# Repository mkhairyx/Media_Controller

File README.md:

# Gesture Based Media controller

## What is it
It's a device that controls your TV using IR signals to mimic your TV's remote control. It detects a gesture and then sends the signal that was coded for that gesture.

## The reason I made it
I made it so I can control different media without having to touch anything with my dirty hands while eating.

## Main modules used
- MCU: An ESP32
- Gesture Sensor: PAJ7620
- Display: OLED 0.96" SSD1306 Display

## Pins and their usages
- GPIO4: IR LED
- GPIO15: IR receiver (TL1838)
- GPIO21: SDA (for both the Gesture Sensor and the display)
- GPIO22: SCL (for both the Gesture Sensor and the display)
- GPIO18: delete button (Internally pulled high)

## How to recreate
You can either make the PCB with is [here](./source/pcbway_production/) or connect everything on a breadboard (while using [this](./README.md#pins-and-their-usages) as a reference) then you can flash the software provided [here](./Source/Arduino/Media_Controller_IRTXnRX) to your ESP32.

## Gestures and their functions
- Move Up / Move Down:<br>
Up Button / Down Button
- Move Left / Move Right:<br>
Left Button / Right Button
- Move Forward:<br>
OK button (for TV)
- Circle Clockwise (CW) / Circle Counter-Clockwise (CCW):<br>
Volume Up Button / Volume Down Button
- Wave (shake):<br>
switch between different TV/PC (Inoperative for now, PC functions will be available in V2)

## Demo Video
A demo vid can be watched here:<br>
https://youtu.be/PJmMg9s-Np0
https://cdn.hackclub.com/01a003da-1a12-7c9f-beef-b3fb1ff95faa/Media%20Controller%20Demo-2.mp4

## Notes
- Please note that AI was used to help with **some** parts of the code and not all of it.
- This is the first version of this project and it doesn't have all of the functions. V2 will have battery percentage measurement, better UI, and will be compatible with both TV and PC with the ability to switch between them.

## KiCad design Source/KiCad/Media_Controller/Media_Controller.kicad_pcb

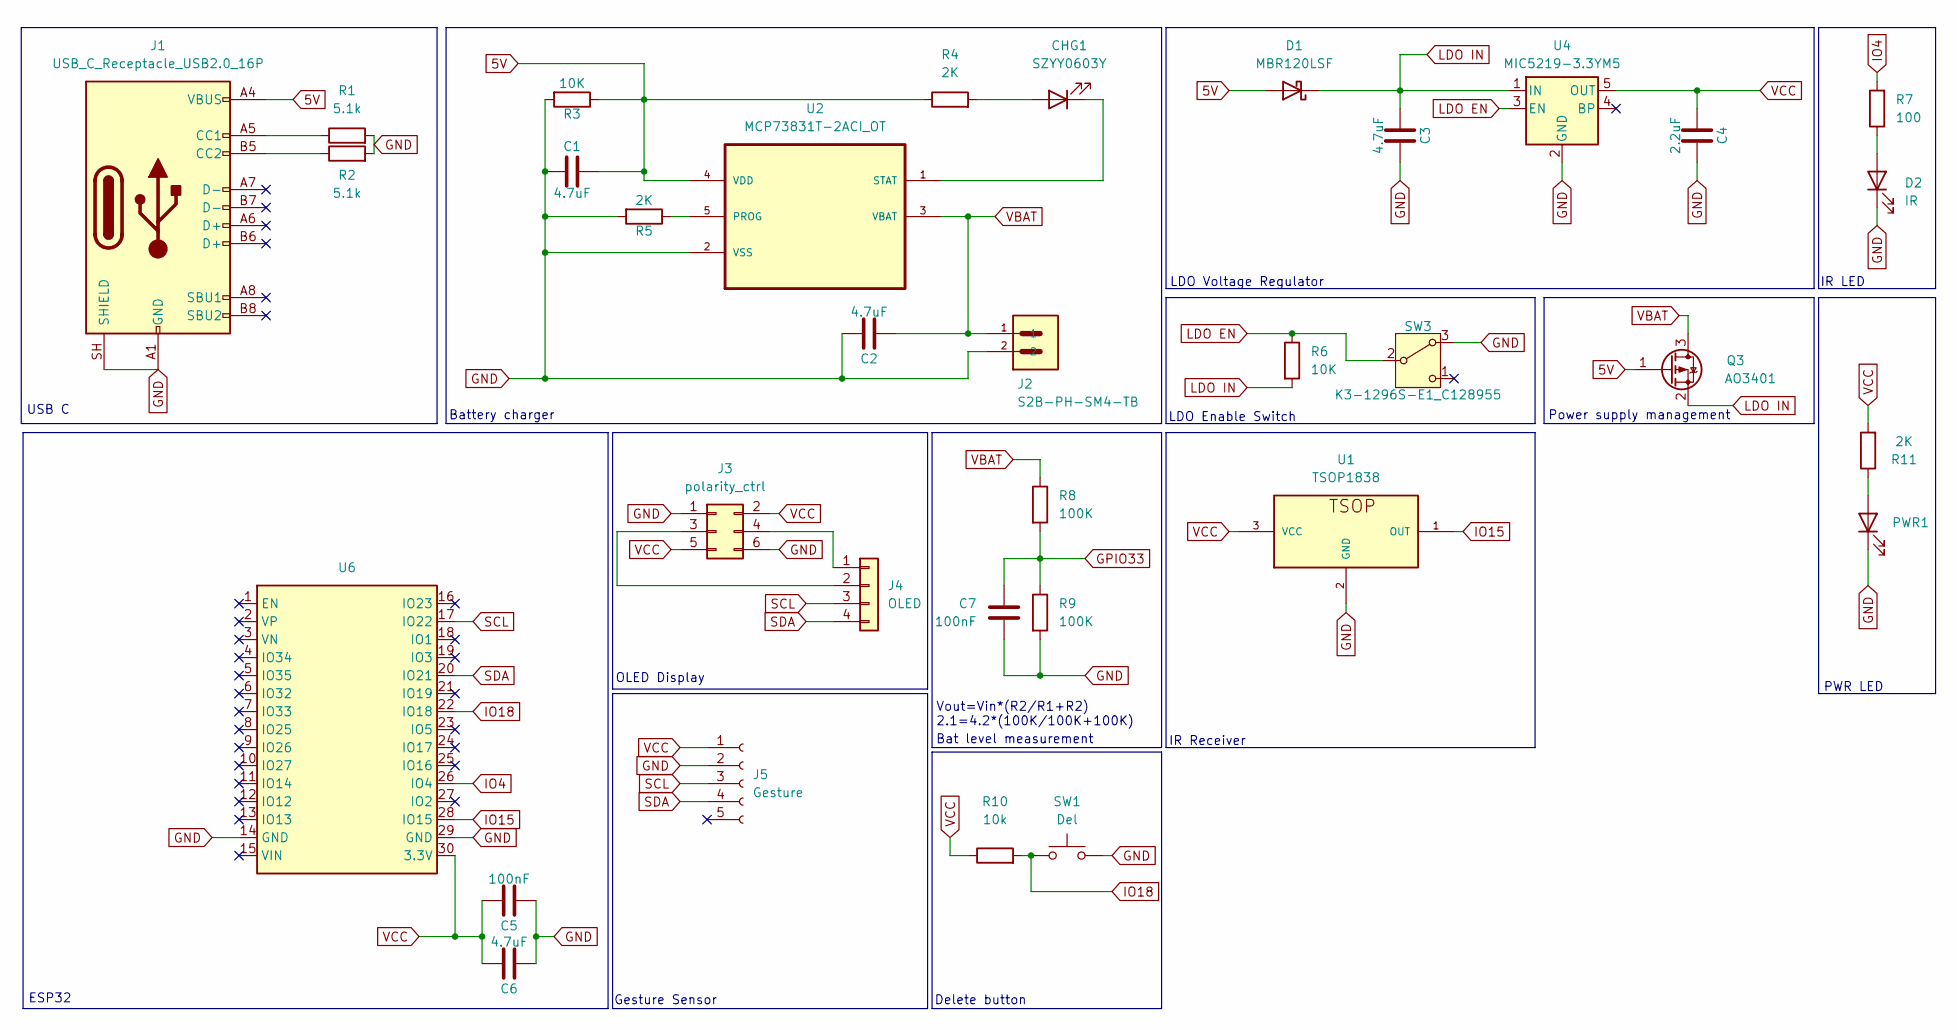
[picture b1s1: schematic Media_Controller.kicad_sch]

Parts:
C1, C2, C3, C6: 4.7uF; C_1206_3216Metric_Pad1.33x1.80mm_HandSolder
C4: 2.2uF; C_0805_2012Metric_Pad1.18x1.45mm_HandSolder
C5, C7: 100nF; C_1206_3216Metric_Pad1.33x1.80mm_HandSolder
CHG1: SZYY0603Y; LED_0805_2012Metric_Pad1.15x1.40mm_HandSolder
D1: MBR120LSF; D_SMA_Handsoldering
D2: IR; LED_D5.0mm
J1: USB_C_Receptacle_USB2.0_16P; USB_C_Receptacle_GCT_USB4105-xx-A_16P_TopMnt_Horizontal
J2: S2B-PH-SM4-TB; JST_EH_B2B-EH-A_1x02_P2.50mm_Vertical
J3: polarity_ctrl; PinHeader_2x03_P2.54mm_Vertical
J4: OLED; PinSocket_1x04_P2.54mm_Vertical
J5: Gesture; PinSocket_1x05_P2.54mm_Vertical
PWR1: SZYY0603Y; LED_0805_2012Metric_Pad1.15x1.40mm_HandSolder
Q3: AO3401; SOT-23
R1, R2: 5.1k; R_Axial_DIN0207_L6.3mm_D2.5mm_P7.62mm_Horizontal
R3, R6: 10K; R_0805_2012Metric_Pad1.20x1.40mm_HandSolder
R4, R5, R11: 2K; R_0805_2012Metric_Pad1.20x1.40mm_HandSolder
R7: 100; R_0805_2012Metric_Pad1.20x1.40mm_HandSolder
R8, R9: 100K; R_0805_2012Metric_Pad1.20x1.40mm_HandSolder
R10: 10k; R_0805_2012Metric_Pad1.20x1.40mm_HandSolder
SW1: Del; SW_PUSH_6mm_H13mm
SW3: K3-1296S-E1_C128955; SW_Slide_SPDT_Angled_CK_OS102011MA1Q
U1: TSOP1838
U2: MCP73831T-2ACI_OT; SOT-23-5_HandSoldering; MPN MCP73831T-2ACI/OT
U4: MIC5219-3.3YM5; SOT-23-5_HandSoldering
U6: ESP32 DevKit

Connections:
5V: C1.2, D1.2 (A), J1.A4 (VBUS), J1.A9 (VBUS), J1.B4 (VBUS), J1.B9 (VBUS), Q3.1 (G), R3.1, R4.1, U2.4 (VDD)
GND: C1.1, C2.2, C3.2, C4.2, C5.1, C6.1, C7.2, D2.1 (K), J1.A1 (GND), J1.A12 (GND), J1.B1 (GND), J1.B12 (GND), J1.SH (SHIELD), J2.2, J3.1, J3.6, J5.2, PWR1.1 (K), R1.2, R2.2, R3.2, R5.2, R9.2, SW1.2, SW3.3 (A), U1.2 (GND), U2.2 (VSS), U4.2 (GND), U6.14 (GND), U6.29 (GND)
GPIO33: C7.1, R8.2, R9.1
IO4: R7.2, U6.26 (IO4)
IO15: U1.1 (OUT), U6.28 (IO15)
IO18: R10.2, SW1.1, U6.22 (IO18)
LDO EN: R6.1, SW3.2 (B), U4.3 (EN)
LDO IN: C3.1, D1.1 (K), Q3.2 (S), R6.2, U4.1 (IN)
unnamed: CHG1.2 (A), R4.2
unnamed: CHG1.1 (K), U2.1 (STAT)
unnamed: D2.2 (A), R7.1
unnamed: J1.A5 (CC1), R1.1
unnamed: J1.B5 (CC2), R2.1
unnamed: J3.3, J4.2
unnamed: J3.4, J4.1
unnamed: PWR1.2 (A), R11.1
unnamed: R5.1, U2.5 (PROG)
SCL: J4.3, J5.3, U6.17 (IO22)
SDA: J4.4, J5.4, U6.20 (IO21)
VBAT: C2.1, J2.1, Q3.3 (D), R8.1, U2.3 (VBAT)
VCC: C4.1, C5.2, C6.2, J3.2, J3.5, J5.1, R10.1, R11.2, U1.3 (VCC), U4.5 (OUT), U6.30 (3.3V)

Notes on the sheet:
PWR LED
OLED Display
Delete button
LDO Enable Switch
Gesture Sensor
Power supply management
ESP32
IR Receiver
IR LED
Battery charger
Bat level measurement
USB C
Vout=Vin*(R2/R1+R2) 2.1=4.2*(100K/100K+100K)
LDO Voltage Regulator

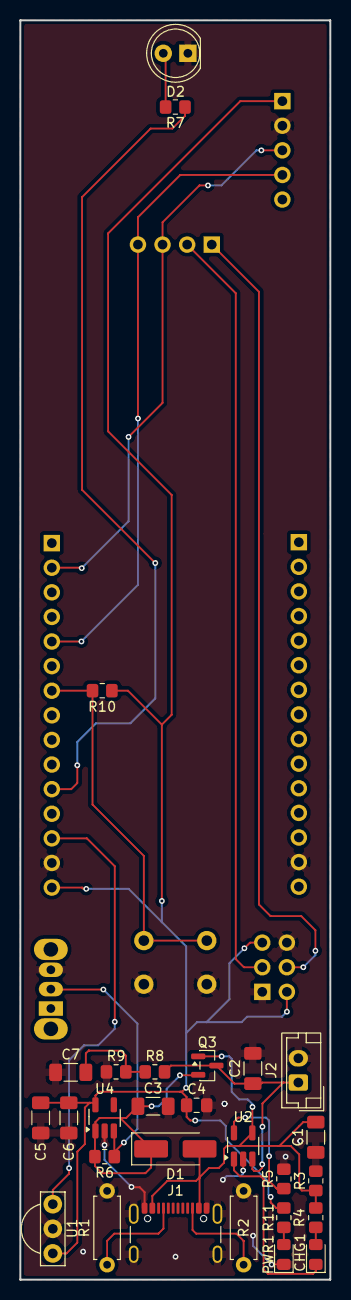
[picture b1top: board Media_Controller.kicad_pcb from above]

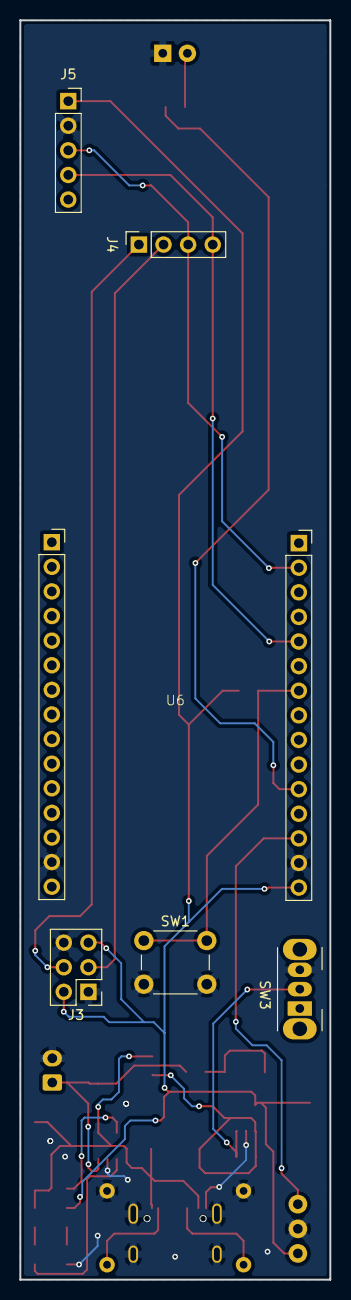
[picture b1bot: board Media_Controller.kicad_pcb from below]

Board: 2 copper layers, 32.0 x 130.0 mm, 34 parts (6 on the bottom side), 21 nets.

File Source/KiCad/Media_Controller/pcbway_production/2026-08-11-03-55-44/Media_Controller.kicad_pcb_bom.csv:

Designator,Quantity,Value,Footprint,Package,MPN,DNP,Mount_Type,Description,KiLib_Generator,Sim.Pins,MF,Price,Check_prices,SnapEDA_Link,MP,Purchase-URL,Availability,MANUFACTURER,OC_FARNELL,SUPPLIER,OC_NEWARK
"C1, C2, C3, C6",4,4.7uF,C_1206_3216Metric_Pad1.33x1.80mm_HandSolder,,,,smt,Unpolarized capacitor,SMD_2terminal_chip_molded,,,,,,,,,,,,
C4,1,2.2uF,C_0805_2012Metric_Pad1.18x1.45mm_HandSolder,,,,smt,Unpolarized capacitor,SMD_2terminal_chip_molded,,,,,,,,,,,,
"C5, C7",2,100nF,C_1206_3216Metric_Pad1.33x1.80mm_HandSolder,,,,smt,Unpolarized capacitor,SMD_2terminal_chip_molded,,,,,,,,,,,,
"CHG1, PWR1",2,SZYY0603Y,LED_0805_2012Metric_Pad1.15x1.40mm_HandSolder,,,,smt,Light emitting diode,SMD_2terminal_chip_molded,1=K 2=A,,,,,,,,,,,
D1,1,MBR120LSF,D_SMA_Handsoldering,,,,smt,Schottky diode,,,,,,,,,,,,,
D2,1,IR,LED_D5.0mm,,,,tht,Light emitting diode,LED/THT,1=K 2=A,,,,,,,,,,,
J1,1,USB_C_Receptacle_USB2.0_16P,USB_C_Receptacle_GCT_USB4105-xx-A_16P_TopMnt_Horizontal,,,,smt,USB 2.0-only 16P Type-C Receptacle connector,,,,,,,,,,,,,
J2,1,S2B-PH-SM4-TB,JST_EH_B2B-EH-A_1x02_P2.50mm_Vertical,None,,,tht,"Connector Header Surface Mount, Right Angle 2 position 0.079 (2.00mm)",connector/JST,,JST Sales,None,https://www.snapeda.com/parts/S2B-PH-SM4-TB/JST/view-part/?ref=eda,https://www.snapeda.com/parts/S2B-PH-SM4-TB/JST/view-part/?ref=snap,S2B-PH-SM4-TB,https://www.snapeda.com/api/url_track_click_mouser/?unipart_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 Sales&part_name=S2B-PH-SM4-TB&search_term=s2b-ph-sm4-tb,In Stock,JST,,,
J3,1,polarity_ctrl,PinHeader_2x03_P2.54mm_Vertical,,,,tht,"Generic connector, double row, 02x03, odd/even pin numbering scheme (row 1 odd numbers, row 2 even numbers), script generated (kicad-library-utils/schlib/autogen/connector/)",connector/pin_header_socket,,,,,,,,,,,,
J4,1,OLED,PinSocket_1x04_P2.54mm_Vertical,,,,tht,"Generic connector, single row, 01x04, script generated (kicad-library-utils/schlib/autogen/connector/)",connector/pin_header_socket,,,,,,,,,,,,
J5,1,Gesture,PinSocket_1x05_P2.54mm_Vertical,,,,tht,"Generic connector, single row, 01x05, script generated",connector/pin_header_socket,,,,,,,,,,,,
Q3,1,AO3401,SOT-23,,,,smt,"-0.18A Id, -60V Vds, P-Channel MOSFET, SOT-23",package/gullwing,,,,,,,,,,,,
"R1, R2",2,5.1k,R_Axial_DIN0207_L6.3mm_D2.5mm_P7.62mm_Horizontal,,,,tht,Resistor,resistor/THT,,,,,,,,,,,,
R10,1,10k,R_0805_2012Metric_Pad1.20x1.40mm_HandSolder,,,,smt,Resistor,SMD_2terminal_chip_molded,,,,,,,,,,,,
"R11, R4, R5",3,2K,R_0805_2012Metric_Pad1.20x1.40mm_HandSolder,,,,smt,Resistor,SMD_2terminal_chip_molded,,,,,,,,,,,,
"R3, R6",2,10K,R_0805_2012Metric_Pad1.20x1.40mm_HandSolder,,,,smt,Resistor,SMD_2terminal_chip_molded,,,,,,,,,,,,
R7,1,100,R_0805_2012Metric_Pad1.20x1.40mm_HandSolder,,,,smt,Resistor,SMD_2terminal_chip_molded,,,,,,,,,,,,
"R8, R9",2,100K,R_0805_2012Metric_Pad1.20x1.40mm_HandSolder,,,,smt,Resistor,SMD_2terminal_chip_molded,,,,,,,,,,,,
SW1,1,Del,SW_PUSH_6mm_H13mm,,,,tht,"Push button switch, generic, two pins",,,,,,,,,,,,,
SW3,1,K3-1296S-E1_C128955,SW_Slide_SPDT_Angled_CK_OS102011MA1Q,,,,tht,"Switch slide, single pole double throw",,,,,,,,,,,,,
U1,1,TSOP1838,TSOP1838,None,,,tht,IR Remote Receiver 38KHz 35m 3-Pin,,,Vishay,None,https://www.snapeda.com/parts/TSOP1838/Vishay/view-part/?ref=eda,https://www.snapeda.com/parts/TSOP1838/Vishay/view-part/?ref=snap,TSOP1838,https://www.snapeda.com/api/url_track_click_mouser/?unipart_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,In Stock,,,,
U2,1,MCP73831T-2ACI_OT,SOT-23-5_HandSoldering,SOT-5,MCP73831T-2ACI/OT,,smt,"TINY INTEGRATED LI-ION/LI-POLY CHARGE MGNT CONTROLLER, 4.2V VREG | Microchip Technology Inc. MCP73831T-2ACI/OT",,,Microchip,None,https://www.snapeda.com/parts/MCP73831T-2ACI/OT/Microchip+Te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,https://www.snapeda.com/parts/MCP73831T-2ACI/OT/Microchip+Te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,MCP73831T-2ACI/OT,https://www.snapeda.com/api/url_track_click_mouser/?unipart_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,In Stock,,1332158,Microchip,56K7045
U4,1,MIC5219-3.3YM5,SOT-23-5_HandSoldering,,,,smt,"500mA low dropout linear regulator, fixed 3.3V output, SOT-23-5",,,,,,,,,,,,,
U6,1,~,ESP32 DevKit,,,,smt,,,,,,,,,,,,,,
